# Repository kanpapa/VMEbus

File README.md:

# VMEbus

This repository contains documentation and sources for running digital's 68000 VME board DVME CPU2. 

Please refer to my blog for more information.  
https://kanpapa.com/2023/08/68000-vme-board1.html

* [DVMECPU2](/DVMECPU2/)
  * Memory map
  * Parts list

* [Hardware test](/hardware_test/)
  * This program sends a Hello world string to the serial port.

* [VME_power](/VME_power/)
  * Kicad data for the printed circuit board to supply power to the VME board.

* [mbed](/mbed/)
  * CPU simulator for investigating address decoders using mbed LPC1768.

* [zBug](/zBug/)
  * zbug monitor source program and ROM image data.

* [EhBASIC for DVMECPU2](/EhBASIC/)
  * Modified [EhBASIC](https://philpem.me.uk/leeedavison/68k/simbasic/index.html) source code for DVMECPU2.
  * Free for personal use only (see readme.txt).

* [images](/images/)
  * Photos data

## Photos

## Caution
The contents of this repository are the result of personal research and are non-guaranteed.

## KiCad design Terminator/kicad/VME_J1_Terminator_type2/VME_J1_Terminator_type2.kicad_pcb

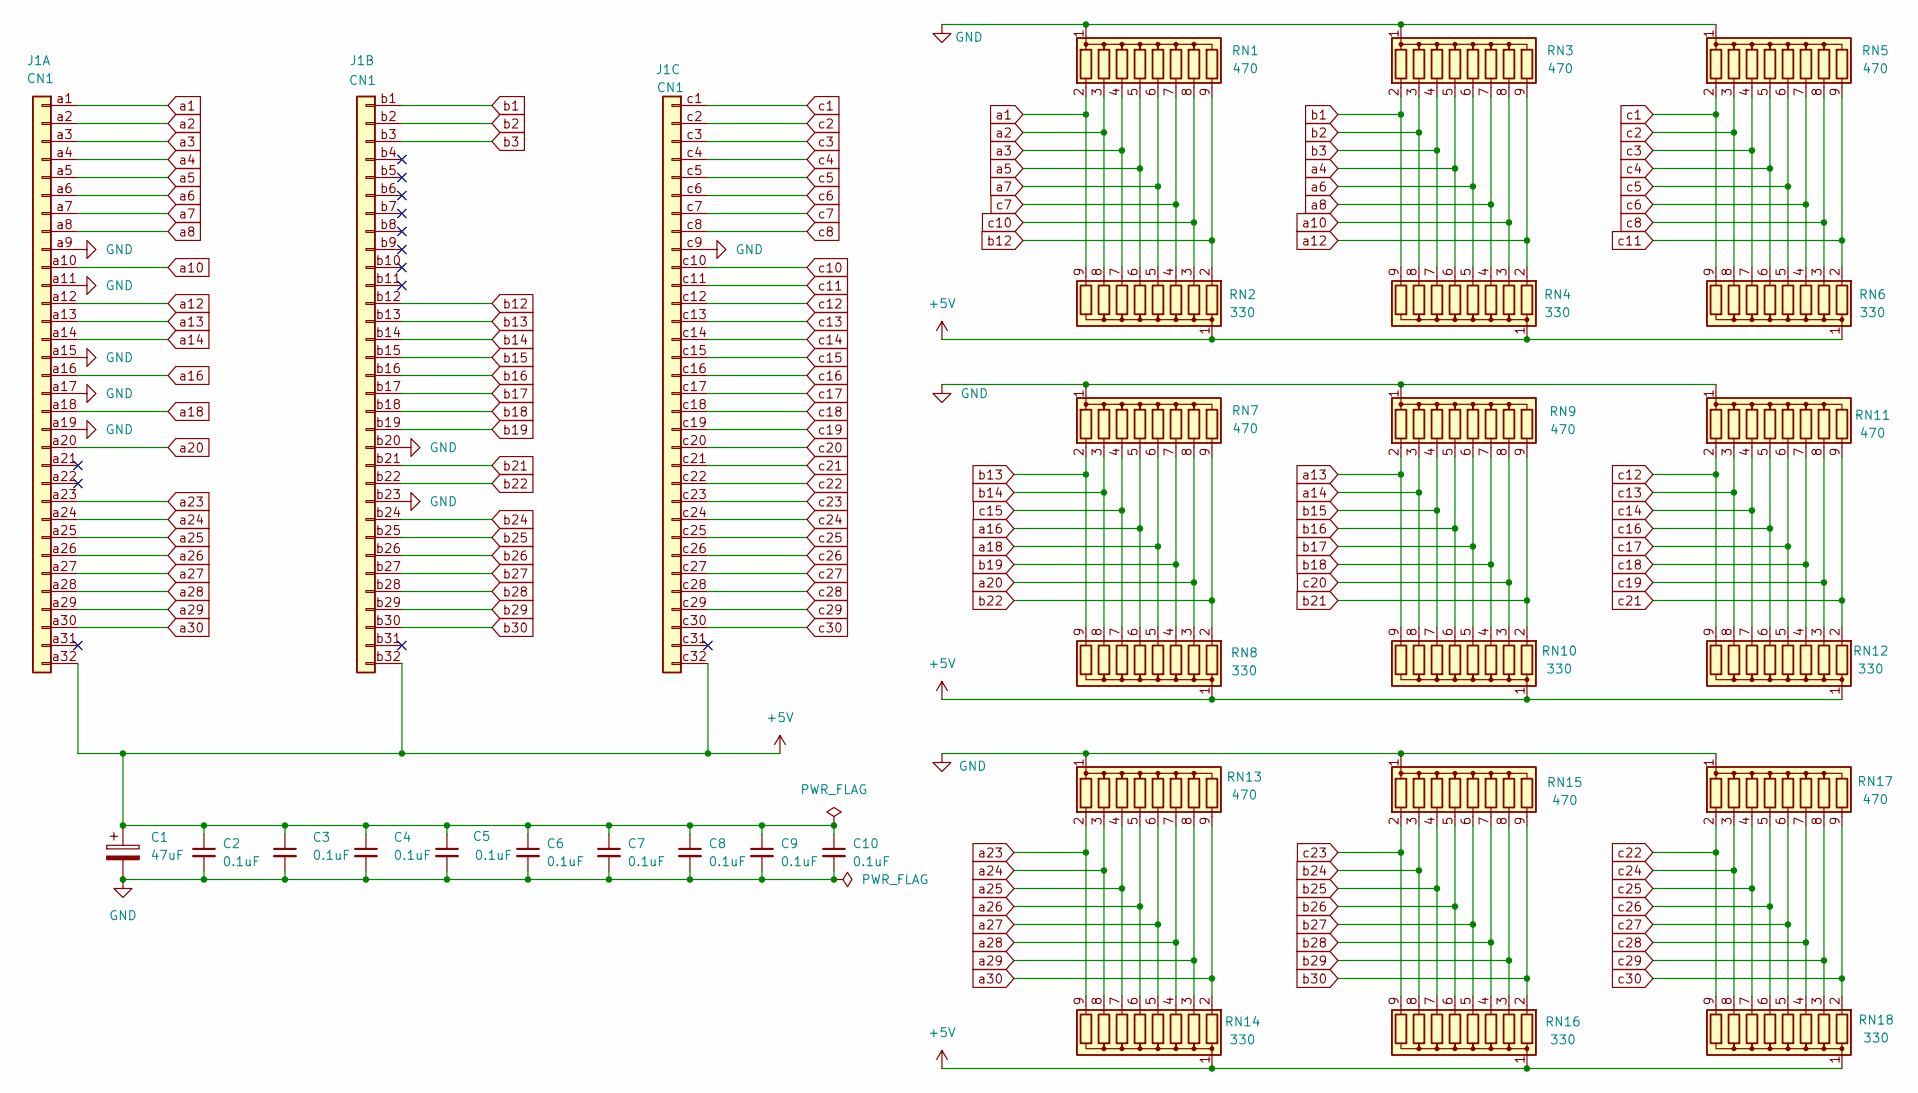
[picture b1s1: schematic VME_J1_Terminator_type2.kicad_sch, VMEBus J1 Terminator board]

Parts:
C1: 47uF; CP_Radial_D6.3mm_P2.50mm
C2, C3, C4, C5, C6, C7, C8, C9, C10: 0.1uF; C_Disc_D3.0mm_W2.0mm_P2.50mm
J1: CN1; DIN41612_C_3x32_Female_Horizontal_THT
RN1, RN3, RN5, RN7, RN9, RN11, RN13, RN15, RN17: 470; R_Array_SIP9
RN2, RN4, RN6, RN8, RN10, RN12, RN14, RN16, RN18: 330; R_Array_SIP9

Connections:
+5V: C1.1, C2.1, C3.1, C4.1, C5.1, C6.1, C7.1, C8.1, C9.1, C10.1, J1.a32, J1.b32, J1.c32, RN2.1 (common), RN4.1 (common), RN6.1 (common), RN8.1 (common), RN10.1 (common), RN12.1 (common), RN14.1 (common), RN16.1 (common), RN18.1 (common)
GND: C1.2, C2.2, C3.2, C4.2, C5.2, C6.2, C7.2, C8.2, C9.2, C10.2, J1.a9, J1.a11, J1.a15, J1.a17, J1.a19, J1.b20, J1.b23, J1.c9, RN1.1 (common), RN3.1 (common), RN5.1 (common), RN7.1 (common), RN9.1 (common), RN11.1 (common), RN13.1 (common), RN15.1 (common), RN17.1 (common)
a1: J1.a1, RN1.2 (R1), RN2.9 (R8)
a2: J1.a2, RN1.3 (R2), RN2.8 (R7)
a3: J1.a3, RN1.4 (R3), RN2.7 (R6)
a4: J1.a4, RN3.5 (R4), RN4.6 (R5)
a5: J1.a5, RN1.5 (R4), RN2.6 (R5)
a6: J1.a6, RN3.6 (R5), RN4.5 (R4)
a7: J1.a7, RN1.6 (R5), RN2.5 (R4)
a8: J1.a8, RN3.7 (R6), RN4.4 (R3)
a10: J1.a10, RN3.8 (R7), RN4.3 (R2)
a12: J1.a12, RN3.9 (R8), RN4.2 (R1)
a13: J1.a13, RN9.2 (R1), RN10.9 (R8)
a14: J1.a14, RN9.3 (R2), RN10.8 (R7)
a16: J1.a16, RN7.5 (R4), RN8.6 (R5)
a18: J1.a18, RN7.6 (R5), RN8.5 (R4)
a20: J1.a20, RN7.8 (R7), RN8.3 (R2)
a23: J1.a23, RN13.2 (R1), RN14.9 (R8)
a24: J1.a24, RN13.3 (R2), RN14.8 (R7)
a25: J1.a25, RN13.4 (R3), RN14.7 (R6)
a26: J1.a26, RN13.5 (R4), RN14.6 (R5)
a27: J1.a27, RN13.6 (R5), RN14.5 (R4)
a28: J1.a28, RN13.7 (R6), RN14.4 (R3)
a29: J1.a29, RN13.8 (R7), RN14.3 (R2)
a30: J1.a30, RN13.9 (R8), RN14.2 (R1)
b1: J1.b1, RN3.2 (R1), RN4.9 (R8)
b2: J1.b2, RN3.3 (R2), RN4.8 (R7)
b3: J1.b3, RN3.4 (R3), RN4.7 (R6)
b12: J1.b12, RN1.9 (R8), RN2.2 (R1)
b13: J1.b13, RN7.2 (R1), RN8.9 (R8)
b14: J1.b14, RN7.3 (R2), RN8.8 (R7)
b15: J1.b15, RN9.4 (R3), RN10.7 (R6)
b16: J1.b16, RN9.5 (R4), RN10.6 (R5)
b17: J1.b17, RN9.6 (R5), RN10.5 (R4)
b18: J1.b18, RN9.7 (R6), RN10.4 (R3)
b19: J1.b19, RN7.7 (R6), RN8.4 (R3)
b21: J1.b21, RN9.9 (R8), RN10.2 (R1)
b22: J1.b22, RN7.9 (R8), RN8.2 (R1)
b24: J1.b24, RN15.3 (R2), RN16.8 (R7)
b25: J1.b25, RN15.4 (R3), RN16.7 (R6)
b26: J1.b26, RN15.5 (R4), RN16.6 (R5)
b27: J1.b27, RN15.6 (R5), RN16.5 (R4)
b28: J1.b28, RN15.7 (R6), RN16.4 (R3)
b29: J1.b29, RN15.8 (R7), RN16.3 (R2)
b30: J1.b30, RN15.9 (R8), RN16.2 (R1)
c1: J1.c1, RN5.2 (R1), RN6.9 (R8)
c2: J1.c2, RN5.3 (R2), RN6.8 (R7)
c3: J1.c3, RN5.4 (R3), RN6.7 (R6)
c4: J1.c4, RN5.5 (R4), RN6.6 (R5)
c5: J1.c5, RN5.6 (R5), RN6.5 (R4)
c6: J1.c6, RN5.7 (R6), RN6.4 (R3)
c7: J1.c7, RN1.7 (R6), RN2.4 (R3)
c8: J1.c8, RN5.8 (R7), RN6.3 (R2)
c10: J1.c10, RN1.8 (R7), RN2.3 (R2)
c11: J1.c11, RN5.9 (R8), RN6.2 (R1)
c12: J1.c12, RN11.2 (R1), RN12.9 (R8)
c13: J1.c13, RN11.3 (R2), RN12.8 (R7)
c14: J1.c14, RN11.4 (R3), RN12.7 (R6)
c15: J1.c15, RN7.4 (R3), RN8.7 (R6)
c16: J1.c16, RN11.5 (R4), RN12.6 (R5)
c17: J1.c17, RN11.6 (R5), RN12.5 (R4)
c18: J1.c18, RN11.7 (R6), RN12.4 (R3)
c19: J1.c19, RN11.8 (R7), RN12.3 (R2)
c20: J1.c20, RN9.8 (R7), RN10.3 (R2)
c21: J1.c21, RN11.9 (R8), RN12.2 (R1)
c22: J1.c22, RN17.2 (R1), RN18.9 (R8)
c23: J1.c23, RN15.2 (R1), RN16.9 (R8)
c24: J1.c24, RN17.3 (R2), RN18.8 (R7)
c25: J1.c25, RN17.4 (R3), RN18.7 (R6)
c26: J1.c26, RN17.5 (R4), RN18.6 (R5)
c27: J1.c27, RN17.6 (R5), RN18.5 (R4)
c28: J1.c28, RN17.7 (R6), RN18.4 (R3)
c29: J1.c29, RN17.8 (R7), RN18.3 (R2)
c30: J1.c30, RN17.9 (R8), RN18.2 (R1)

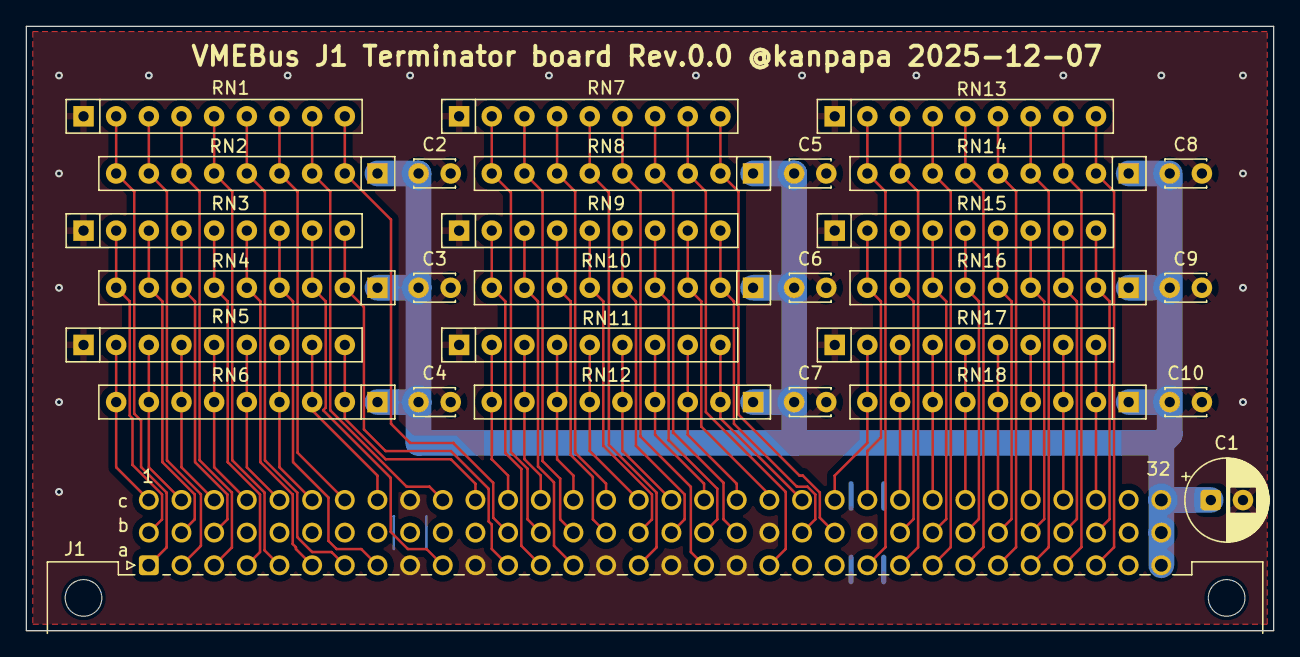
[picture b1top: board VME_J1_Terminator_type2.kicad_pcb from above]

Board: 2 copper layers, 97.0 x 47.0 mm, 29 parts (0 on the bottom side), 74 nets.

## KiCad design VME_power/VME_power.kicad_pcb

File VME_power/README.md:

# VME_power

VMEボード P1コネクタのブレイクアウトボードです。VMEボードへの電源の供給およびP1コネクタの信号をすべて引き出せます。

## ボードのアイデア

* VMEbusのP1コネクタから電源（5V, 12V, -12V）を供給します。
* P1コネクタの全信号をコネクタに引き出します。

## KiCadデータ

KiCADで設計からガーバーデータの作成を行いました。

* [回路図](./VME_power_sch.pdf)
* [BOM](./VME_power.csv)

## Breakout boardのイメージ図

## 完成したBreakout board

## Disclaimer
The contents of this repository are the result of personal research and are provided "as is" without any warranty.

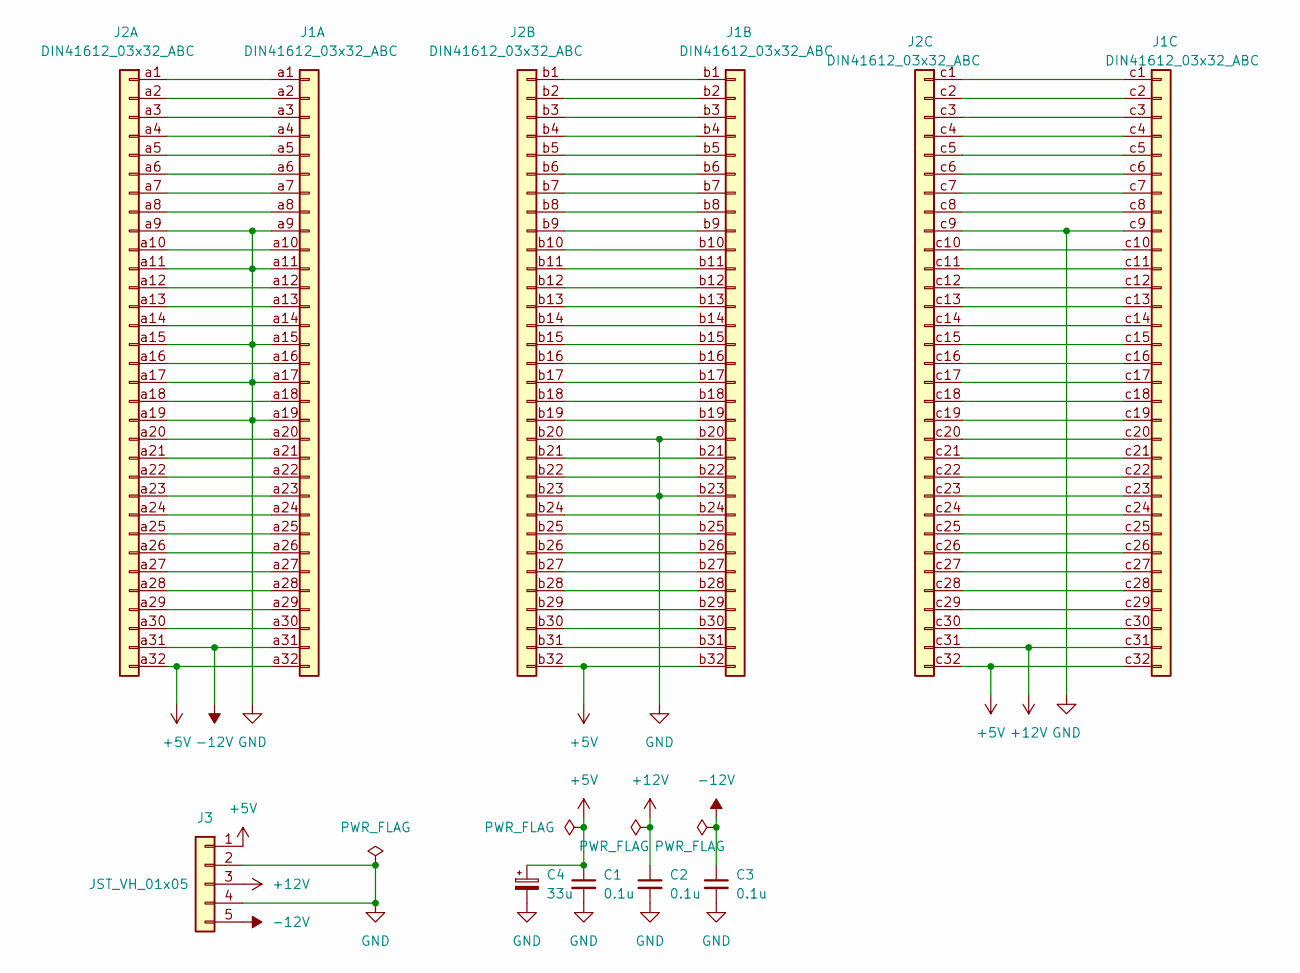
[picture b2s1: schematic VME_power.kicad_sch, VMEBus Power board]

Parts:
C1, C2, C3: 0.1u; C_Disc_D3.4mm_W2.1mm_P2.50mm
C4: 33u; C_Radial_D4.0mm_H5.0mm_P1.50mm
J1: DIN41612_03x32_ABC; DIN41612_C_3x32_Male_Horizontal_THT
J2: DIN41612_03x32_ABC; DIN41612_C_3x32_Female_Vertical_THT
J3: JST_VH_01x05; JST_VH_B5P-VH_1x05_P3.96mm_Vertical

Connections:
+5V: C1.1, C4.1, J1.a32, J1.b32, J1.c32, J2.a32, J2.b32, J2.c32, J3.1
+12V: C2.1, J1.c31, J2.c31, J3.3
-12V: C3.1, J1.a31, J2.a31, J3.5
GND: C1.2, C2.2, C3.2, C4.2, J1.a9, J1.a11, J1.a15, J1.a17, J1.a19, J1.b20, J1.b23, J1.c9, J2.a9, J2.a11, J2.a15, J2.a17, J2.a19, J2.b20, J2.b23, J2.c9, J3.2, J3.4
unnamed: J1.a1, J2.a1
unnamed: J1.a2, J2.a2
unnamed: J1.a3, J2.a3
unnamed: J1.a4, J2.a4
unnamed: J1.a5, J2.a5
unnamed: J1.a6, J2.a6
unnamed: J1.a7, J2.a7
unnamed: J1.a8, J2.a8
unnamed: J1.a10, J2.a10
unnamed: J1.a12, J2.a12
unnamed: J1.a13, J2.a13
unnamed: J1.a14, J2.a14
unnamed: J1.a16, J2.a16
unnamed: J1.a18, J2.a18
unnamed: J1.a20, J2.a20
unnamed: J1.a21, J2.a21
unnamed: J1.a22, J2.a22
unnamed: J1.a23, J2.a23
unnamed: J1.a24, J2.a24
unnamed: J1.a25, J2.a25
unnamed: J1.a26, J2.a26
unnamed: J1.a27, J2.a27
unnamed: J1.a28, J2.a28
unnamed: J1.a29, J2.a29
unnamed: J1.a30, J2.a30
unnamed: J1.b1, J2.b1
unnamed: J1.b2, J2.b2
unnamed: J1.b3, J2.b3
unnamed: J1.b4, J2.b4
unnamed: J1.b5, J2.b5
unnamed: J1.b6, J2.b6
unnamed: J1.b7, J2.b7
unnamed: J1.b8, J2.b8
unnamed: J1.b9, J2.b9
unnamed: J1.b10, J2.b10
unnamed: J1.b11, J2.b11
unnamed: J1.b12, J2.b12
unnamed: J1.b13, J2.b13
unnamed: J1.b14, J2.b14
unnamed: J1.b15, J2.b15
unnamed: J1.b16, J2.b16
unnamed: J1.b17, J2.b17
unnamed: J1.b18, J2.b18
unnamed: J1.b19, J2.b19
unnamed: J1.b21, J2.b21
unnamed: J1.b22, J2.b22
unnamed: J1.b24, J2.b24
unnamed: J1.b25, J2.b25
unnamed: J1.b26, J2.b26
unnamed: J1.b27, J2.b27
unnamed: J1.b28, J2.b28
unnamed: J1.b29, J2.b29
unnamed: J1.b30, J2.b30
unnamed: J1.b31, J2.b31
unnamed: J1.c1, J2.c1
unnamed: J1.c2, J2.c2
unnamed: J1.c3, J2.c3
unnamed: J1.c4, J2.c4
unnamed: J1.c5, J2.c5
unnamed: J1.c6, J2.c6
unnamed: J1.c7, J2.c7
unnamed: J1.c8, J2.c8
unnamed: J1.c10, J2.c10
unnamed: J1.c11, J2.c11
unnamed: J1.c12, J2.c12
unnamed: J1.c13, J2.c13
unnamed: J1.c14, J2.c14
unnamed: J1.c15, J2.c15
unnamed: J1.c16, J2.c16
unnamed: J1.c17, J2.c17
unnamed: J1.c18, J2.c18
unnamed: J1.c19, J2.c19
unnamed: J1.c20, J2.c20
unnamed: J1.c21, J2.c21
unnamed: J1.c22, J2.c22
unnamed: J1.c23, J2.c23
unnamed: J1.c24, J2.c24
unnamed: J1.c25, J2.c25
unnamed: J1.c26, J2.c26
unnamed: J1.c27, J2.c27
unnamed: J1.c28, J2.c28
unnamed: J1.c29, J2.c29
unnamed: J1.c30, J2.c30

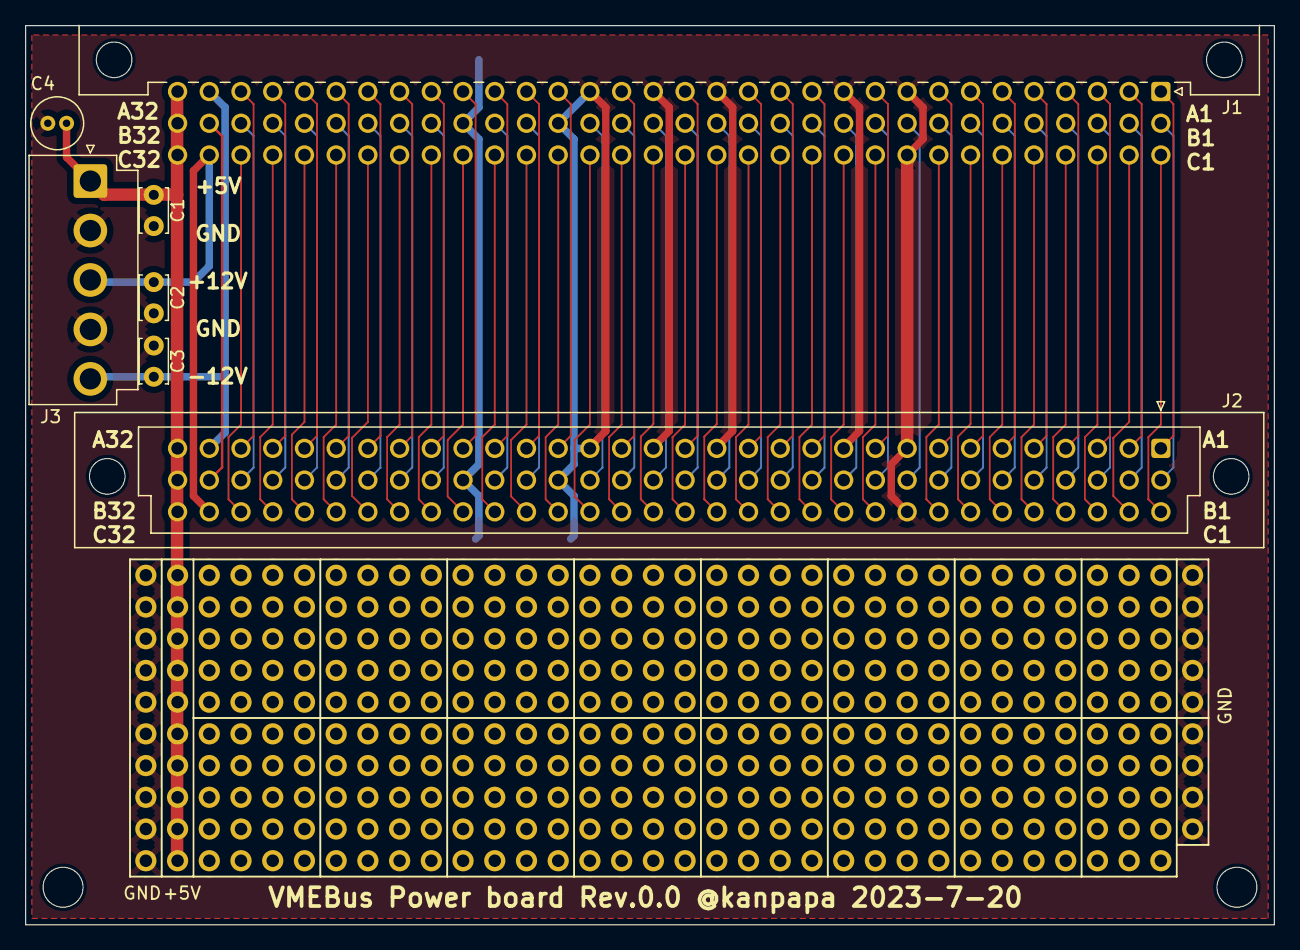
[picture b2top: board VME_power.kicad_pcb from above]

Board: 2 copper layers, 100.0 x 72.0 mm, 9 parts (0 on the bottom side), 87 nets.

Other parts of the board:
MH1, MH2: MountingHole_3.2mm_M3

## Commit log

2023-07-29 Added KiCAD data for VME power board.
2023-08-19 1st commit
2023-09-04 Added mbed-os-m68kemu
2023-09-09 Added hardware test programs
2023-09-09 Added zBug
2023-09-09 Remove Arduino directory
2023-09-09 Added ROM image files
2023-09-10 Removed unused programs
2023-09-10 Added DVMECPU2 data
2023-09-12 Added photo image
2023-09-12 Added images
2025-01-31 Added BOM
2025-11-26 Added EhBASIC for DVMECPU2.
2025-12-07 Added VMEBus terminator off board
2025-12-11 Update README with new photos and descriptions
    Added images and descriptions for DVMECPU2 and VME Power board.
2025-12-27 Fix blog link in README
    Updated the blog link for more information.
2026-06-14 BOMを修正
2026-06-14 VME_powerのREADME.mdを作成
2026-06-14 写真を追加
2026-06-14 リンクを追加
